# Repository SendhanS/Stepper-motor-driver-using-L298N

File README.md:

# Stepper-motor-driver-using-L298N
Two Phase Bipolar Stepper Motor controller based on L298
Uses L298N and L297 for at VS-12V and VSS-5V
THIS IS DONE AS PRACTISE AND NOT BEEN TESTED OR FABRICATED.

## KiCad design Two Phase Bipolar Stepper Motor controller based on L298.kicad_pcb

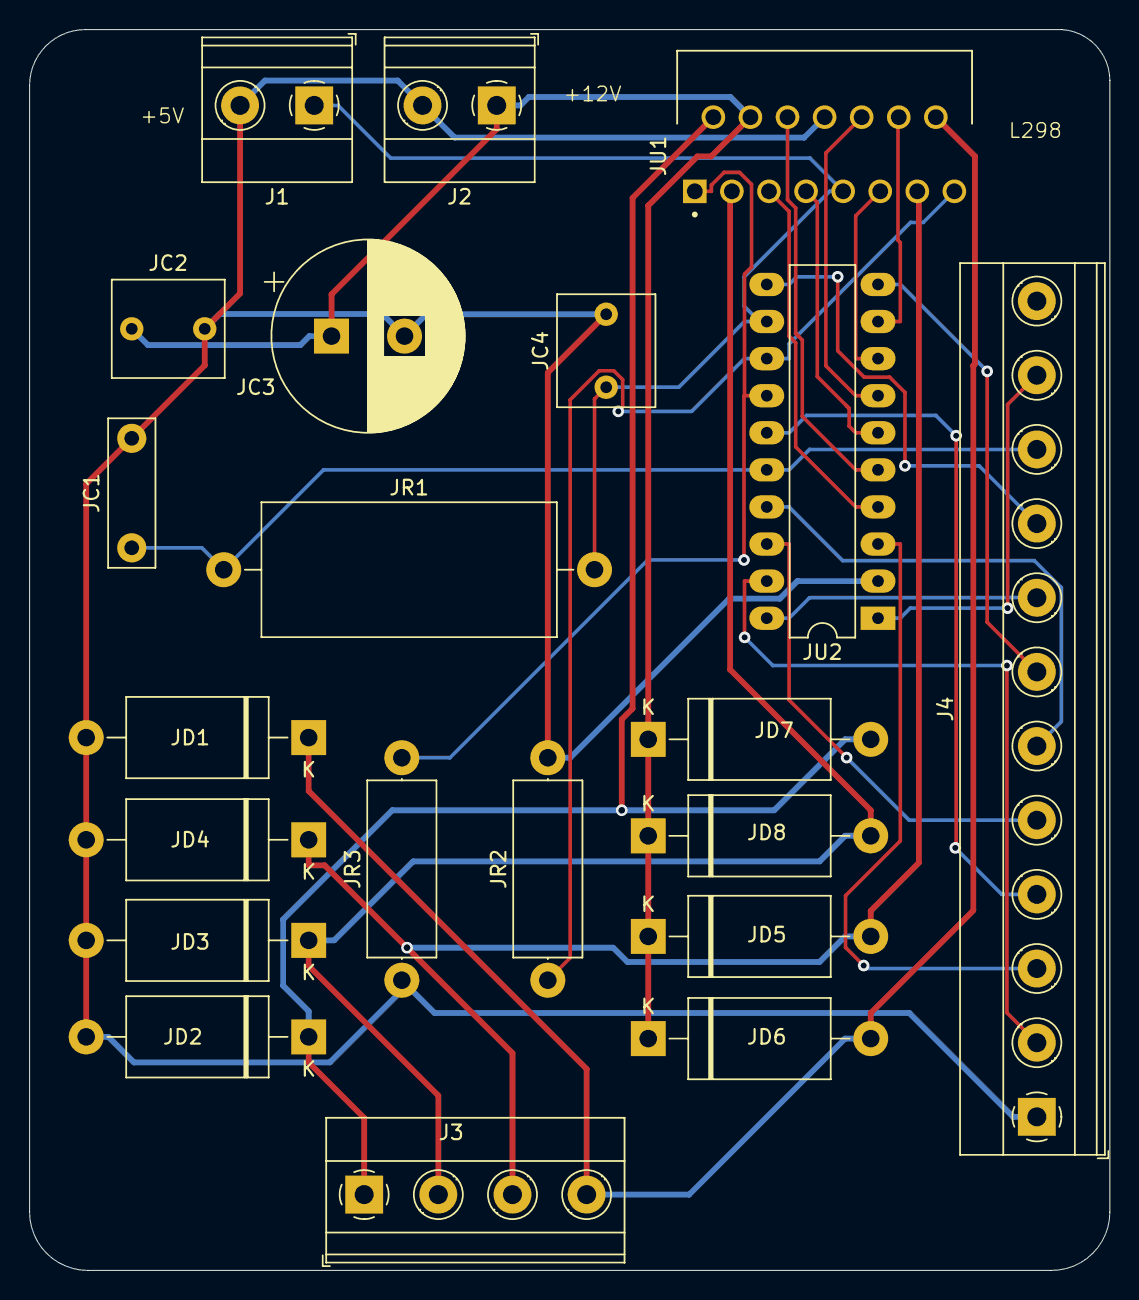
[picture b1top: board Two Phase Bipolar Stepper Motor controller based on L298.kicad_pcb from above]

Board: 2 copper layers, 74.0 x 85.0 mm, 21 parts (0 on the bottom side), 25 nets.

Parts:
J1, J2: Screw_Terminal_01x02; TerminalBlock_Phoenix_MKDS-1,5-2-5.08_1x02_P5.08mm_Horizont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
J3: Screw_Terminal_01x04; TerminalBlock_Phoenix_MKDS-1,5-4-5.08_1x04_P5.08mm_Horizont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
J4: Screw_Terminal_01x12; TerminalBlock_Phoenix_MKDS-1,5-12-5.08_1x12_P5.08mm_Horizon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
JC1: 3.3nf; C_Rect_L10.0mm_W3.0mm_P7.50mm_FKS3_FKP3
JC2, JC4: 100nf; C_Rect_L7.5mm_W6.5mm_P5.00mm
JC3: 470uf; CP_Radial_D13.0mm_P5.00mm
JD1, JD2, JD3, JD4, JD5, JD6, JD7, JD8: D_Schottky; D_DO-27_P15.24mm_Horizontal
JR1: 22k; R_Axial_DIN0922_L20.0mm_D9.0mm_P25.40mm_Horizontal
JR2, JR3: 0.5ohm; R_Axial_DIN0414_L11.9mm_D4.5mm_P15.24mm_Horizontal
JU1: L298N; TO127P2020X500X2100-15
JU2: L297; CERDIP-20_W7.62mm_SideBrazed_LongPads

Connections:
/CW: J4.6, JU2.17 (CW)
/Clk: J4.5, JU2.18 (CLOCK)
/Ctrl: J4.9, JU2.11 (CONTROL)
/EN: J4.7, JU2.10 (ENABLE)
/Half: J4.2, JU2.19 (HALF)
/Home: J4.3, JU2.3 (HOME)
/Osc: J4.10, JC1.1, JR1.1, JU2.16 (OSC)
/RESET: J4.8, JU2.20 (RESET)
/Rs1: JR3.2, JU1.1 (SENSE_A), JU2.14 (SENS1)
/Rs2: JR2.1, JU1.15 (SENSE_B), JU2.13 (SENS2)
/Sync: J4.11, JU2.1 (SYNC)
/Vref: J4.4, JU2.15 (Vref)
GND: J1.2, J2.2, J4.1, JC1.2, JC2.2, JC3.2, JC4.2, JD1.2 (A), JD2.2 (A), JD3.2 (A), JD4.2 (A), JR2.2, JR3.1, JU1.8 (GND), JU2.2 (GND)
unnamed: J3.1, JD2.1 (K), JD7.2 (A), JU1.2 (OUT1)
unnamed: J3.2, JD3.1 (K), JD8.2 (A), JU1.3 (OUT2)
unnamed: J3.3, JD4.1 (K), JD5.2 (A), JU1.13 (OUT3)
unnamed: J3.4, JD1.1 (K), JD6.2 (A), JU1.14 (OUT4)
unnamed: JU1.5 (IN1), JU2.4 (A)
unnamed: JU1.7 (IN2), JU2.6 (B)
unnamed: JU1.10 (IN3), JU2.7 (C)
unnamed: JU1.12 (IN4), JU2.9 (D)
unnamed: JU1.6 (ENA), JU2.5 (INH1)
unnamed: JU1.11 (ENB), JU2.8 (INH2)
VS: J2.1, JC2.1, JC3.1, JD5.1 (K), JD6.1 (K), JD7.1 (K), JD8.1 (K), JU1.4 (VS)
VSS: J1.1, JC4.1, JR1.2, JU1.9 (VSS), JU2.12 (Vs)
